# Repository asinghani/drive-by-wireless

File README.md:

# Distributed Embedded Final Project

UWB drive-by-wireless

## Build Instructions

1. Clone pico-sdk and pico-extras and put them in your environment variables as `PICO_SDK_PATH` and `PICO_EXTRAS_PATH`. Also clone FreeRTOS-Kernel, `smp` branch and put its path as `FREERTOS_KERNEL_PATH`

2. `cd firmware`

3. `rm -r build; mkdir build; cd build` (its safest to delete and re-make the build directory every time because CMake caches things incorrectly sometimes)

4. `cmake .. && make -j8` (this will build all 3 targets - cockpit, steering, and drivetrain)

5. This should yield `zone_cockpit.uf2`, `zone_steering.uf2`, and `zone_drivetrain.uf2` which can be flashed to the boards.

## File Structure

```
- firmware/ (the directory for the firmware)
    - main.c (main entry point, shouldn't put any more code into this file)
    - utils.h (utility functions for math, safety, etc.)
    - config.h (configuration of GPIO pins, etc.)
    - FreeRTOSConfig.h
    - z_cockpit/
        - main_cockpit.c (entry point for cockpit zone)
    - z_drivetrain/
        - main_drivetrain.c (entry point for drivetrain zone)
    - z_steering/
        - main_steering.c (entry point for steering zone)
    - common/ (common stuff)
        - freertos_callbacks.c
    - peripherals/ (drivers for hardware peripherals)
        - testpoints.h (driver for test points)

- experimental/ (for test programs)

- scripts/ (scripts to run on a host machine)
    - proxy_gui.py (the steering wheel proxy, to run on Windows)

- hardware/ (hardware / CAD files)
    - 449pcb_v1/ (PCB CAD)
    - schematic.pdf (board schematic, for easy reference)

```

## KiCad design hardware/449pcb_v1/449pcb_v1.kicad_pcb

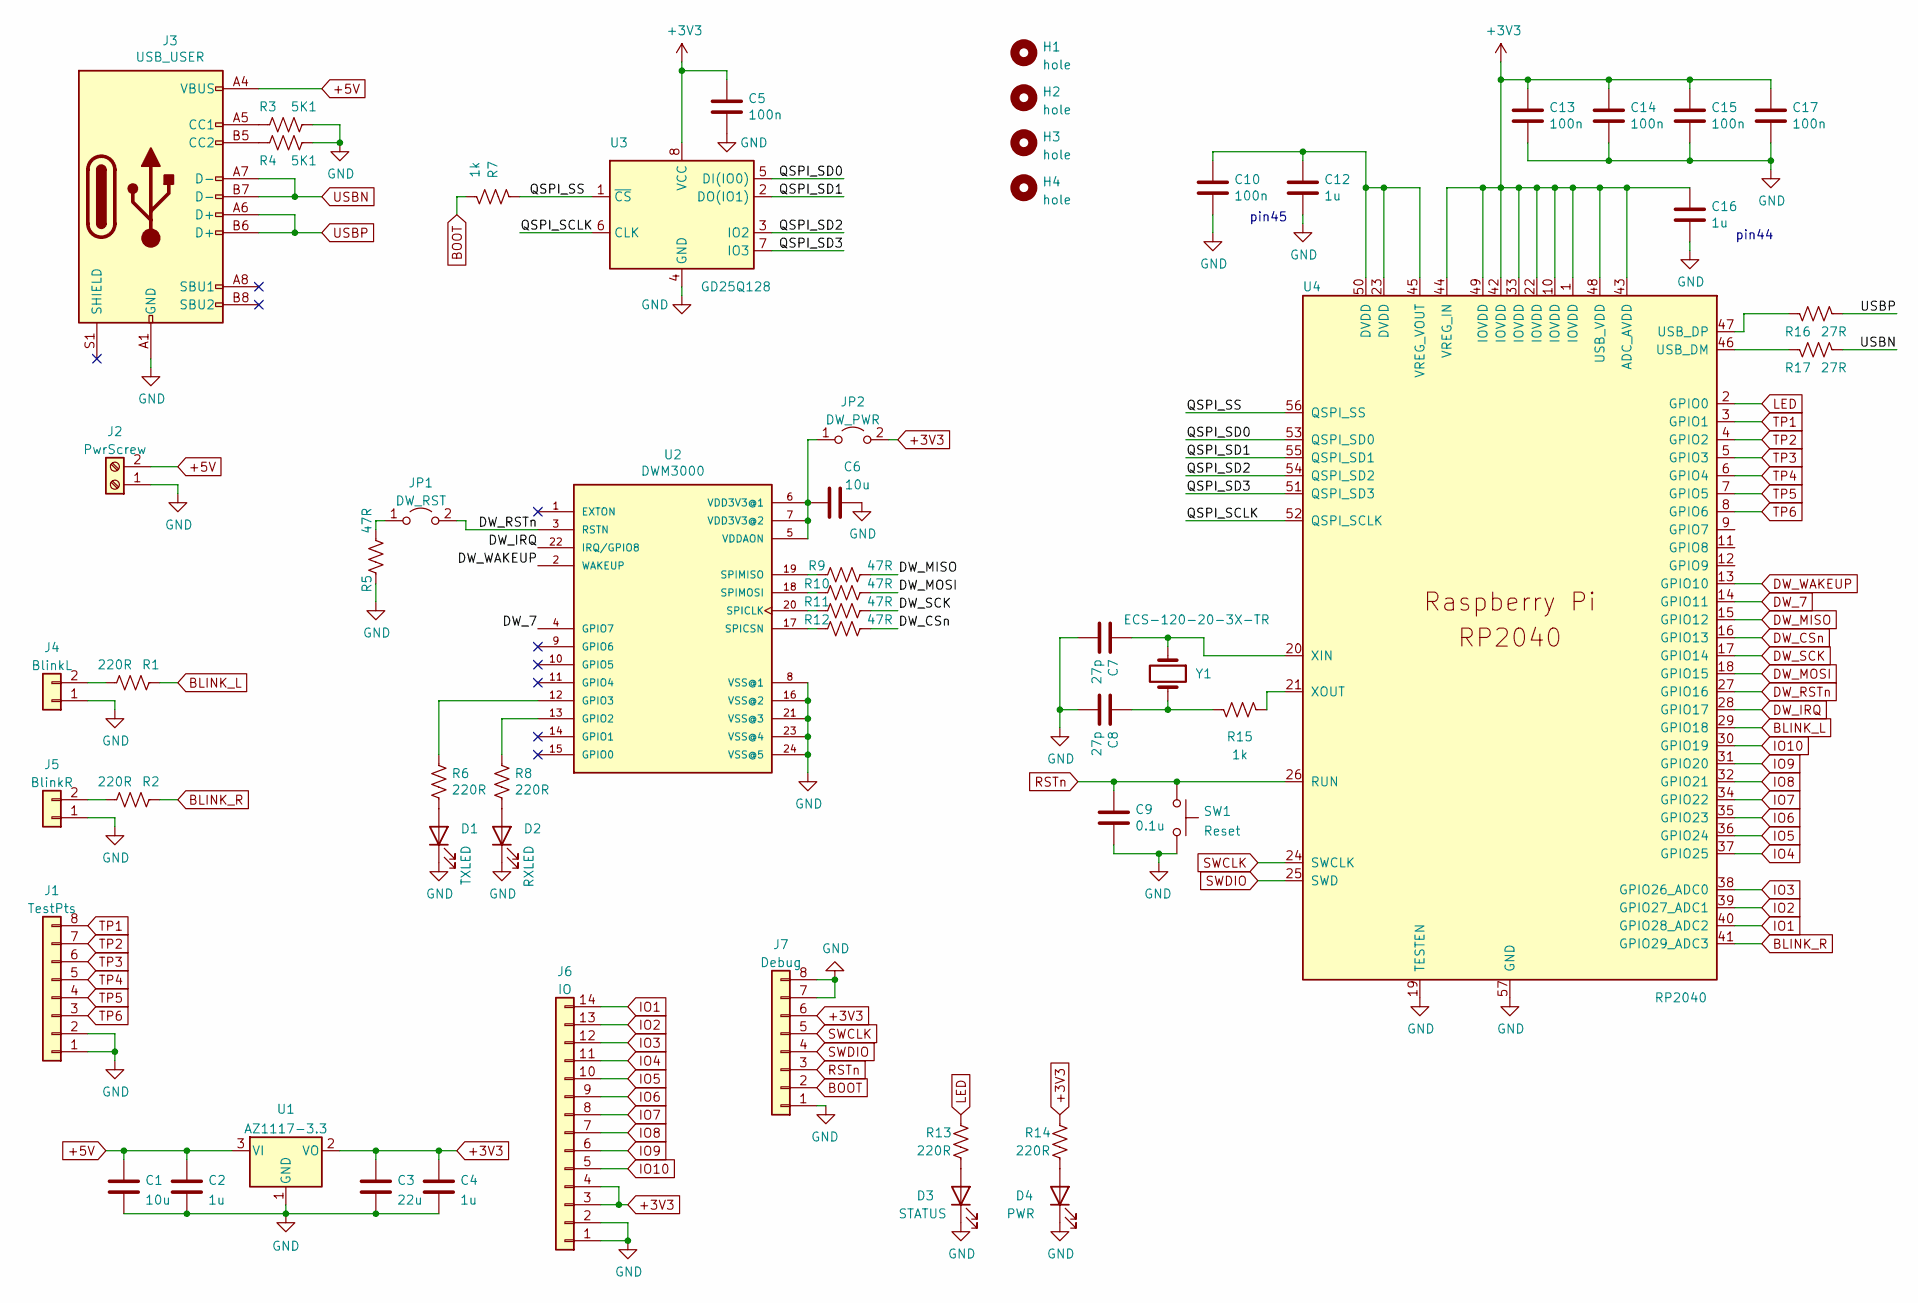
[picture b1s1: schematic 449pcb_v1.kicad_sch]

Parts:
C1, C6: 10u; C_0603_1608Metric
C2, C4, C12, C16: 1u; C_0603_1608Metric
C3: 22u; C_0603_1608Metric
C5, C10, C13, C14, C15, C17: 100n; C_0603_1608Metric
C7, C8: 27p; C_0603_1608Metric
C9: 0.1u; C_0603_1608Metric
D1: TXLED; LED_0805_2012Metric
D2: RXLED; LED_0805_2012Metric
D3: STATUS; LED_0805_2012Metric
D4: PWR; LED_0805_2012Metric
H1, H2, H3, H4: hole; MountingHole_3.2mm_M3_Pad_Via
J1: TestPts; PinHeader_1x08_P2.54mm_Vertical
J2: PwrScrew; TerminalBlock_4Ucon_1x02_P3.50mm_Horizontal
J3: USB_USER; USB_C_HRO-31-M-12_nofront
J4: BlinkL; PinHeader_1x02_P2.54mm_Vertical
J5: BlinkR; PinHeader_1x02_P2.54mm_Vertical
J6: IO; PinHeader_1x14_P2.54mm_Vertical
J7: Debug; PinHeader_1x08_P2.54mm_Vertical
JP1: DW_RST; PinHeader_1x02_P2.54mm_Vertical
JP2: DW_PWR; PinHeader_1x02_P2.54mm_Vertical
R1, R2, R6, R8, R13, R14: 220R; R_0603_1608Metric
R3, R4: 5K1; R_0603_1608Metric
R5, R9, R10, R11, R12: 47R; R_0603_1608Metric
R7, R15: 1k; R_0603_1608Metric
R16, R17: 27R; R_0603_1608Metric
SW1: Reset; SW_SPST_PTS810
U1: AZ1117-3.3; SOT-223-3_TabPin2
U2: DWM3000
U3: GD25Q128; SOIC-8_5.23x5.23mm_P1.27mm
U4: RP2040; RP2040-QFN-56
Y1: ECS-120-20-3X-TR; XTAL_ECS-120-20-3X-TR

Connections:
+3V3: C3.1, C4.1, C5.1, C13.1, C14.1, C15.1, C16.1, C17.1, J6.3, J6.4, J7.6, JP2.2 (B), R14.1, U1.2 (VO), U3.8 (VCC), U4.1 (IOVDD), U4.10 (IOVDD), U4.22 (IOVDD), U4.33 (IOVDD), U4.42 (IOVDD), U4.43 (ADC_AVDD), U4.44 (VREG_IN), U4.48 (USB_VDD), U4.49 (IOVDD)
+5V: C1.1, C2.1, J2.2, J3.A4 (VBUS), J3.A9 (VBUS), J3.B4 (VBUS), J3.B9 (VBUS), U1.3 (VI)
/QSPI_SCLK: U3.6 (CLK), U4.52 (QSPI_SCLK)
/QSPI_SD0: U3.5 (DI(IO0)), U4.53 (QSPI_SD0)
/QSPI_SD1: U3.2 (DO(IO1)), U4.55 (QSPI_SD1)
/QSPI_SD2: U3.3 (IO2), U4.54 (QSPI_SD2)
/QSPI_SD3: U3.7 (IO3), U4.51 (QSPI_SD3)
/QSPI_SS: R7.2, U3.1 (~CS), U4.56 (QSPI_SS)
BLINK_L: R1.1, U4.29 (GPIO18)
BLINK_R: R2.1, U4.41 (GPIO29_ADC3)
BOOT: J7.2, R7.1
DW_7: U2.4 (GPIO7), U4.14 (GPIO11)
DW_CSn: R12.1, U4.16 (GPIO13)
DW_IRQ: U2.22 (IRQ/GPIO8), U4.28 (GPIO17)
DW_MISO: R9.1, U4.15 (GPIO12)
DW_MOSI: R10.1, U4.18 (GPIO15)
DW_RSTn: JP1.2 (B), U2.3 (RSTN), U4.27 (GPIO16)
DW_SCK: R11.1, U4.17 (GPIO14)
DW_WAKEUP: U2.2 (WAKEUP), U4.13 (GPIO10)
GND: C1.2, C2.2, C3.2, C4.2, C5.2, C6.1, C7.2, C8.2, C9.2, C10.2, C12.2, C13.2, C14.2, C15.2, C16.2, C17.2, D1.1 (K), D2.1 (K), D3.1 (K), D4.1 (K), J1.1, J1.2, J2.1, J3.A1 (GND), J3.A12 (GND), J3.B1 (GND), J3.B12 (GND), J4.1, J5.1, J6.1, J6.2, J7.1, J7.7, J7.8, R3.2, R4.2, R5.2, SW1.2, U1.1 (GND), U2.8 (VSS@1), U2.16 (VSS@2), U2.21 (VSS@3), U2.23 (VSS@4), U2.24 (VSS@5), U3.4 (GND), U4.19 (TESTEN), U4.57 (GND)
IO1: J6.14, U4.40 (GPIO28_ADC2)
IO2: J6.13, U4.39 (GPIO27_ADC1)
IO3: J6.12, U4.38 (GPIO26_ADC0)
IO4: J6.11, U4.37 (GPIO25)
IO5: J6.10, U4.36 (GPIO24)
IO6: J6.9, U4.35 (GPIO23)
IO7: J6.8, U4.34 (GPIO22)
IO8: J6.7, U4.32 (GPIO21)
IO9: J6.6, U4.31 (GPIO20)
IO10: J6.5, U4.30 (GPIO19)
LED: R13.1, U4.2 (GPIO0)
unnamed: C6.2, JP2.1 (A), U2.5 (VDDAON), U2.6 (VDD3V3@1), U2.7 (VDD3V3@2)
unnamed: C7.1, U4.20 (XIN), Y1.1
unnamed: C8.1, R15.2, Y1.2
unnamed: C10.1, C12.1, U4.23 (DVDD), U4.45 (VREG_VOUT), U4.50 (DVDD)
unnamed: D1.2 (A), R6.2
unnamed: D2.2 (A), R8.2
unnamed: J3.A5 (CC1), R3.1
unnamed: J3.B5 (CC2), R4.1
unnamed: J4.2, R1.2
unnamed: J5.2, R2.2
unnamed: JP1.1 (A), R5.1
unnamed: R6.1, U2.12 (GPIO3)
unnamed: R8.1, U2.13 (GPIO2)
unnamed: R9.2, U2.19 (SPIMISO)
unnamed: R10.2, U2.18 (SPIMOSI)
unnamed: R11.2, U2.20 (SPICLK)
unnamed: R12.2, U2.17 (SPICSN)
unnamed: D3.2 (A), R13.2
unnamed: D4.2 (A), R14.2
unnamed: R15.1, U4.21 (XOUT)
unnamed: R17.2, U4.46 (USB_DM)
unnamed: R16.2, U4.47 (USB_DP)
RSTn: C9.1, J7.3, SW1.1, U4.26 (RUN)
SWCLK: J7.5, U4.24 (SWCLK)
SWDIO: J7.4, U4.25 (SWD)
TP1: J1.8, U4.3 (GPIO1)
TP2: J1.7, U4.4 (GPIO2)
TP3: J1.6, U4.5 (GPIO3)
TP4: J1.5, U4.6 (GPIO4)
TP5: J1.4, U4.7 (GPIO5)
TP6: J1.3, U4.8 (GPIO6)
USBN: J3.A7 (D-), J3.B7 (D-), R17.1
USBP: J3.A6 (D+), J3.B6 (D+), R16.1

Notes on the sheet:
pin44
pin45

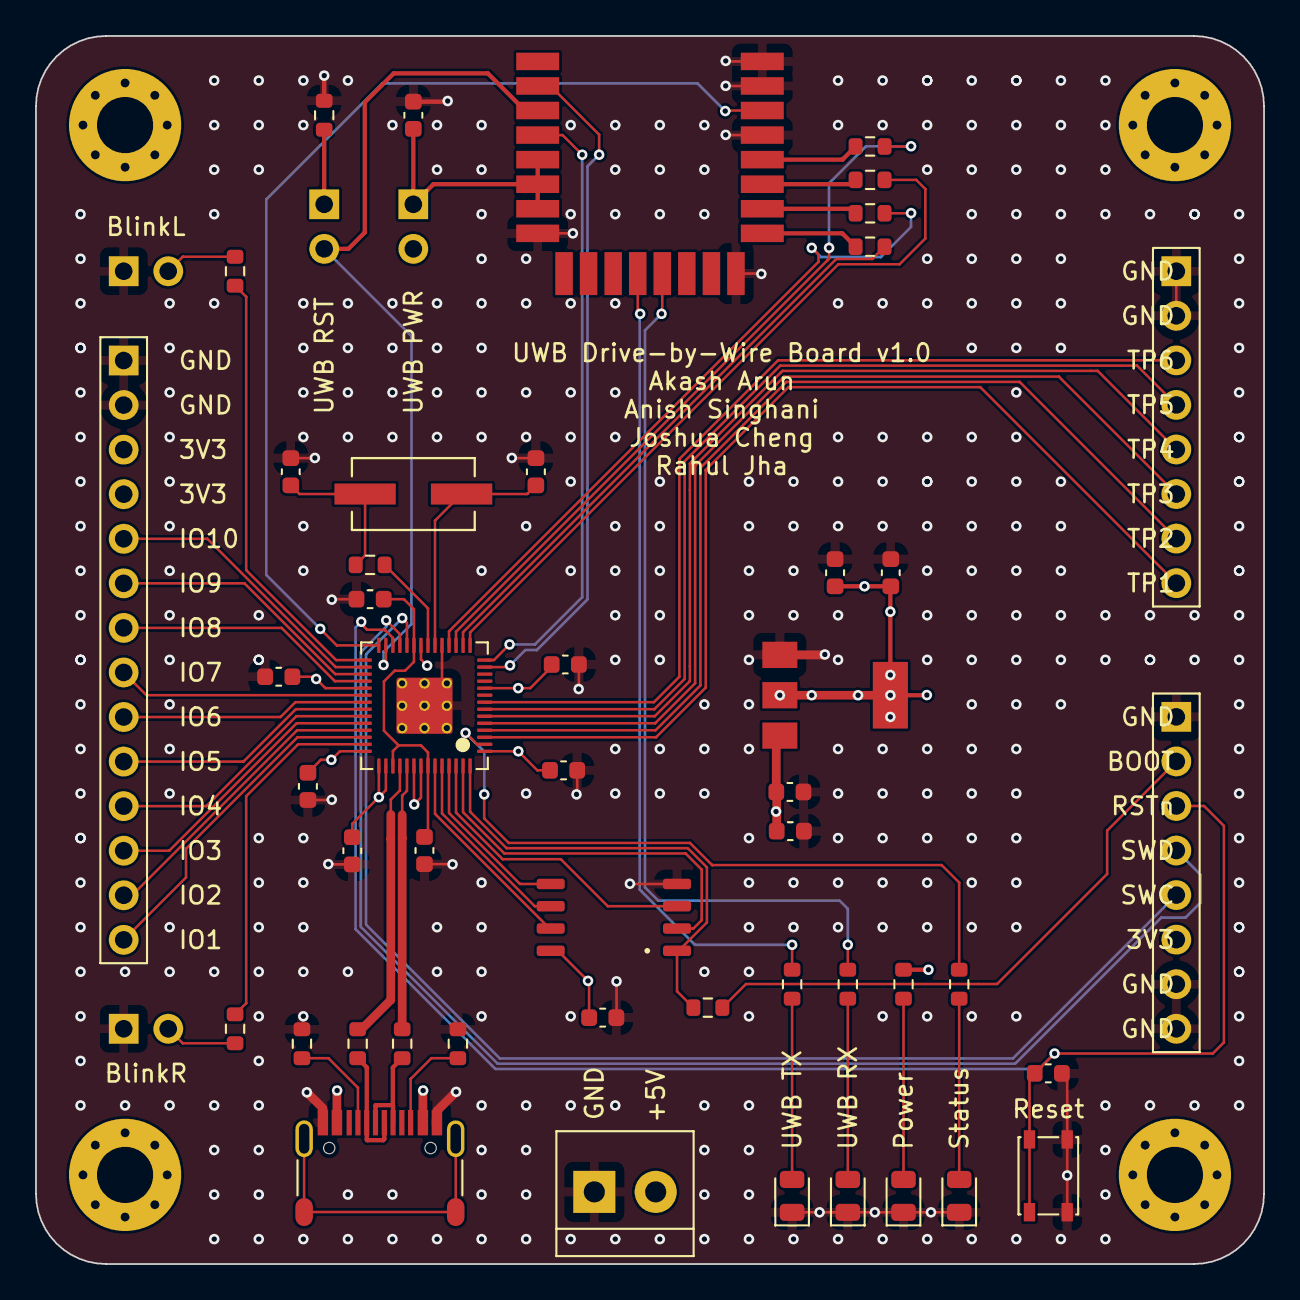
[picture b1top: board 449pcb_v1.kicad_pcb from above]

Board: 4 copper layers, 70.0 x 70.0 mm, 56 parts (0 on the bottom side), 64 nets.

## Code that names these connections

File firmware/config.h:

#ifndef CONFIG_H
#define CONFIG_H

#define IO_1 28
#define IO_2 27
#define IO_3 26
#define IO_4 25
#define IO_5 24
#define IO_6 23
#define IO_7 22
#define IO_8 21
#define IO_9 20
#define IO_10 19

// Maximum packet loss before failure state
#define MAX_COMM_FAILURES 5
#define COMM_TIMEOUT_MS 80

// Blinker rates
#define ERROR_BLINKER_RATE_MS 150
#define BLINKER_RATE_MS 500

// Blinker control config
#define STEER_THRESH1 30
#define STEER_THRESH2 60

// Cockpit zone config
#define STEERING_UART uart1
#define STEERING_RX IO_8
#define STEERING_TX IO_9

// Steering zone config
#define STEERING_SERVO_IO IO_10
#define STEERING_SERVO_CENTER 1385 // Determined experimentally
#define STEERING_SERVO_RANGE 300
#define STEERING_FEEDBACK_IO IO_1
#define STEERING_FEEDBACK_ADC 2 // ch2 = gpio28

// Drivetrain zone config
#define DRIVETRAIN_EN  IO_8
#define DRIVETRAIN_IN1 IO_9
#define DRIVETRAIN_IN2 IO_10
#define VMON_VBAT IO_1
#define VMON_VBAT_ADC 2 // ch2 = gpio28
#define VMON_5V   IO_2
#define VMON_5V_ADC   1 // ch1 = gpio27

#define DRIVETRAIN_LED_STRIP_UART uart1
#define DRIVETRAIN_LED_STRIP_TX IO_5

// Calibrated emperically
#define VMON_VBAT_SCALE 0.00618871
#define VMON_5V_SCALE 0.00619207

// Blinker I/O pins
#define IO_BLINKL 18
#define IO_BLINKR 29

// UWB I/O pins
#define IO_DW_WAKEUP 10
#define IO_DW_7 11
#define IO_DW_CSn 13
#define IO_DW_RSTn 16
#define IO_DW_IRQ 17

// Test-point I/O pins
#define IO_STATUS 0
#define IO_TP1 1
#define IO_TP2 2
#define IO_TP3 3
#define IO_TP4 4
#define IO_TP5 5
#define IO_TP6 6

// Test point definitions
#define ZC_TP_USB_IN  1
#define ZC_TP_USB_OUT 2
#define ZC_TP_UWB_RX  3
#define ZC_TP_UWB_TX  4

#define ZS_TP_UWB_RX     1
#define ZS_TP_UWB_TX     2
#define ZS_TP_STEER_SET  3
#define ZS_TP_FORCE_READ 4

#define ZD_TP_UWB_RX     1
#define ZD_TP_UWB_TX     2
#define ZD_TP_MOTOR_SET  3
#define ZD_TP_IS_BRAKE   4

#define ZDZS_TP_BLINK_L  5
#define ZDZS_TP_BLINK_R  6

// UWB config
#define UWB_PIN_MISO 12
#define UWB_PIN_CS   13
#define UWB_PIN_SCK  14
#define UWB_PIN_MOSI 15
#define UWB_PIN_RSTN 16
#define UWB_SPI_PORT spi1

// Microseconds to raise test-point for
#define TP_TIME_US 100

#define ZID_COCKPIT 0
#define ZID_STEERING 1
#define ZID_DRIVETRAIN 2

#ifdef ZONE_COCKPIT
#define ZONE_ID ZID_COCKPIT 
#endif

#ifdef ZONE_STEERING
#define ZONE_ID ZID_STEERING
#endif

#ifdef ZONE_DRIVETRAIN
#define ZONE_ID ZID_DRIVETRAIN
#endif

#endif

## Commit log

2022-11-07 Steering test
2022-11-07 Steering proxy works
2022-11-23 add hardware dir
2022-11-24 build works with 3 zones
2022-11-24 project build
2022-11-24 uart interface
2022-11-24 steering wheel test script updates
2022-11-24 steering threads in cockpit zone
2022-11-24 Pwm motor and servo code
2022-11-25 integrate steering
2022-11-29 Implemented UWB functions with TDMA. Certain issues with reliability that need further testing
2022-12-02 added_blinker_fsm
2022-12-03 added main_drivetrain task
2022-12-03 minor fix in blinker fsm
2022-12-03 small fix in main_drivertrain
2022-12-03 small change in drivertian
2022-12-03 modifications to config
2022-12-03 removed direction
2022-12-03 drivetrain_motor files
2022-12-03 drivetrain zone fully integrated with freertos need to test it
2022-12-03 add car CAD
2022-12-03 add steering emulator script
2022-12-03 integrate with uwb
2022-12-03 uwb debug
2022-12-03 many bugfixes
2022-12-04 blinky blinky
2022-12-04 encryption test added
2022-12-04 bonks
2022-12-04 add diagnostics thread
2022-12-04 integrate TP
2022-12-04 MUH SECURITAH
2022-12-04 add handling of wheel timeouts
2022-12-04 blinker unit tests
2022-12-04 remove led
2022-12-04 add RGB LEDs
2022-12-04 Added uwb unit test script
2022-12-08 add test code
2022-12-08 Added UWB Unit Test
